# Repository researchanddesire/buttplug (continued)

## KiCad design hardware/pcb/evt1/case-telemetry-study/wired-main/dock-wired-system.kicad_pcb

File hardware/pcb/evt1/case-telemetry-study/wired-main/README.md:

# EVT wired dock Main

The cradle uses its four existing contacts for PC programming and standalone telemetry, with no cradle radio or antenna. The ESP32-C3 remains the USB device in both modes. A full-speed host on a separate RP2040 handles local USB while the STM32L071 retains the screen, buttons, watchdog and UV controls. Both upstream choices use the existing `CONTACT_5V` and ground. The RP2040 has no VBUS source tied to either connector.

The first build should use deliberate local mode selection. A host PC can advertise 1.5 A or 3 A, so `SOURCE_OK` only qualifies available power. It does not authorize taking the USB pair from a computer. A separate hardware PC lock clamps the local-enable logic low even with the two processors stalled. The host rail currently starts whenever qualified power and the lock/reset permissives are present. That lets the STM32 request local mode over the isolated two-wire interface. An independent local power request could reduce PC-mode draw in a later revision. The prototype recovery fixture must make the two shorting pads accessible with the product on the dock and the lid open, then power-cycle the dock with the short held. An enclosure-level access solution is still open.

## Data and recovery

U151 is the onsemi FSUSB42MUX, MSOP-10. Its common D+ and D− go to J102.3/.2. The first channel goes to J101 through retained U121. The second goes to RP2040 pins 47/46 through individual 27 Ω resistors at the RP2040. The common contact side gets separate low-capacitance shunt protection near J102. Its clamp returns to ground. U121 remains on the PC side with its existing `HOST_5V` reference. The switch has an independent active-low enable, a published 2 ns minimum break-before-make under the datasheet fixture conditions, and ±2 µA per-port power-off leakage over the stated test range. The 2 ns prevents overlap under those conditions. Firmware uses a much longer open interval for a planned USB detach.

At reset, the RP2040 request and blank outputs are low. With valid Main power, the switch defaults to PC. On startup use the existing delayed `CC_ENABLE` as the Main rail qualifier. A hardware falling `SOURCE_OK`, `SAFE_RESETn`, rail-valid or PC-lock condition removes local selection regardless of firmware. A forced or brownout transition can end a transfer. Hold the hardware PC lock during a service power-cycle before plug ROM entry if the dock is unresponsive.

In normal service, keep PC selected until the user requests local mode, the new branch is healthy, and the RP2040 USB host is initialized. Assert `USB_BREAK` for an initial 100 ms fixture interval, switch select while open, then remove the break. Return to PC by the same sequence after stopping local I/O. Clear the locally cached current reading on detach or timeout. If qualified source power is unavailable, return an unavailable state and keep PC ownership. Local and PC data access are exclusive. A PC-driven read can supply its own measurements during programming or diagnostics.

The existing Espressif console implements CDC over the native USB Serial/JTAG composite function. Espressif documents VID/PID `303a:1001` for its development-board example. TinyUSB's RP2040 host controller and CDC-ACM class are available. Identify the actual plug descriptors and endpoint/interface numbers before binding code. Enable the ACM host path, whitelist the intended device using the enumerated descriptor, and leave the vendor JTAG interface for the PC. Leave TinyUSB `CFG_TUH_CDC_LINE_CONTROL_ON_ENUM` undefined and avoid automatic DTR/RTS changes during local mounting because the ESP32-C3 USB Serial/JTAG interprets control line transitions for reset. Confirm hardware Power/Mode ROM entry and direct PC flashing with both case MCU reset points held and the recovery lock applied.

[RP2040 datasheet](https://datasheets.raspberrypi.com/rp2040/rp2040-datasheet.pdf) · [Raspberry Pi hardware design](https://pip-assets.raspberrypi.com/categories/814-rp2040/documents/RP-008279-DS-2-hardware-design-with-rp2040.pdf) · [onsemi FSUSB42](https://www.onsemi.com/pdf/datasheet/fsusb42-d.pdf) · [TinyUSB CDC host source](https://github.com/hathach/tinyusb/blob/master/src/class/cdc/cdc_host.c) · [Espressif USB console](https://docs.espressif.com/projects/esp-idf/en/stable/esp32c3/api-guides/usb-serial-jtag-console.html) · [Espressif descriptor example](https://docs.espressif.com/projects/rust/no_std-training/02_1_hardware.html) · [Espressif reset behavior](https://docs.espressif.com/projects/esptool/en/latest/esp32c3/esptool/advanced-options.html)

## Power

The existing hardware-qualified Type-C gate controls the separate `USB_HOST_5V` branch from the existing `HOST_5V` input. TPS2553QDBVRQ1 ILIM is tied directly to IN, the datasheet's 50/75/100 mA DC setting. The host target is at most 40 mA measured at J101 as a branch increment, giving 10 mA against the published minimum limit. This is a test limit. Raspberry Pi's BOOTSEL device-mode measurements give 21 mA at the sum of listed maximum average chip-rail values. The vendor's other workload exceeds 50 mA summed and neither workload represents local host traffic. Qualify actual clock speed, boot, QSPI flash, attach/reset, CDC traffic, SWD servicing, temperature and inrush. In particular, firmware does not write external flash during normal local service.

Reserve 104 mA for the new branch and all added control loads when qualified. At default USB100, the host branch is physically disabled and the existing 70 mA device and 10 mA UI allocations remain. A separate 1 mA allowance covers always-on additions in that mode. The 81 mA steady-state sum is separate from suspend, inrush, dynamic source downgrade, and recovery at a depleted plug battery. The existing device hardware limit can be as low as 34 mA in that mode. The existing PC bypass cannot guarantee standards compliance across USB suspend merely by meeting 100 mA while active.

To retain local USB during UV on a 1.5 A source, the proposed matching population is Main R107 40.2 kΩ 0.1% and UV R401/R501 both 4.22 Ω 1%. The new study computes both the fault ceiling and regulated UV operating point using the same physical path boundaries as the frozen source budget. The source limit and UV LED current must be considered as one assembly choice. The reduced drive requires fresh optical, leakage and thermal validation. Firmware must use the same 4.22 Ω conversion. Never fit a 104 mA branch alongside the frozen 34.8 kΩ and 3.65 Ω configuration for 1.5 A operation.

A separate TPS7A2033PDBVR LDO supplies the RP2040 and flash. Its 3.3 V output tolerance is ±1.5% in regulation. Verify at least 3.60 V at LDO IN and 3.135 V at RP2040 USB_VDD over load, transients and temperature. A local supervisor with a separate rail-valid output holds RUN low through bring-up. Decouple each IOVDD pin, both DVDD pins, USB_VDD and ADC_AVDD. Retain the Raspberry Pi 1 µF regulator input and output capacitors; use at least 1 µF effective local LDO input/output capacitance as the assembly acceptance. Reserve 10 µF nominal at the 3.3 V host regulator output and keep the bulk and startup profile in the inrush test. A contact-side rail monitor qualifies host attachment from J102.4. Its calculated falling threshold is 4.058–4.282 V, and the estimated rising upper corner is 4.408 V. Continuity and voltage at the actual plug contacts remain independent bench checks.

[TPS2553-Q1 datasheet](https://www.ti.com/lit/ds/symlink/tps2553-q1.pdf) · [TPS7A20 datasheet](https://www.ti.com/lit/ds/symlink/tps7a20.pdf) · [Frozen power budget](../../dock-safety/power-budget.json)

## Placement and bring-up

The mechanical read-only probe found a candidate B.Cu 20 × 20 × 1.5 mm volume centered at dock X−21/Y43. Its nominal floor clearance is 0.9 mm. Keep RP2040, ABM8-272-T3 crystal, 15 pF loads and 1 kΩ damping resistor on the same face and immediately adjacent to XIN/XOUT. The exact 6.3 × 3.6 mm mux courtyard passes at F.Cu X2/Y17 with 1.35 mm to the nearest rigid component. The central X0/Y17 site fails the 0.30 mm U114 courtyard margin. The X2 site still crosses the limiter return via. Both host and mux need routing and checks against the final populated native model, including ground reference continuity and the existing VBUS/cutoff routing. See the [package models and provenance](PACKAGE-MODELS.md).

Expose RP2040 SWDIO, SWCLK, RUN, GND and local VTREF as service pads for a target-powered probe. Fit the 10 kΩ external flash CS pull-up and expose BOOTSEL on the flash CS through 1 kΩ; the primary assembly programming plan is SWD while the local branch is qualified. A local BOOTSEL pad is not a second exposed USB programming connector. Keep the existing STM32 SWD and plug physical Power/Mode paths.

## Native KiCad source

Open [the transport schematic](dock-wired-transport.kicad_sch) with its
[project](dock-wired-transport.kicad_pro) to trace the connections across
Main, the display lid and the two UV boards. The transport and Main views
share six sheet files. [Native checks](native-checks.json) record zero KiCad
10.0.8 ERC findings in both views and verify that every Main terminal agrees
with the transport netlist. The combined `native.xml` retains all 303
components and 1,077 terminals for firmware, harness and UV checks. The
[wired firmware targets](../../../../../dock-firmware/wired-main/README.md)
add I²C mode selection and fresh temperature on the display. Winbond stencil
review, PCB routing, installed access and powered USB/UV tests remain open.

Open [the working EVT Main project](dock-wired-system.kicad_pro) for the
[six-sheet schematic](dock-wired-system.kicad_sch) and
[active PCB](dock-wired-system.kicad_pcb). Finish routing and fit on this
board. It incorporates the fixed-position
oscillator and crossing routes, contact-voltage valid, limiter-fault
readback, ground stitching and the latest 3.3 V supply branches. The host
I²C clock, the qualified USB enable branch from U153.3 to U157 and the
always-on reset control from U157.13 to U163.6 are routed.
R163.1 joins the USB enable net. Host I²C data joins U201.6, U162.2 and
pull-up R165.1. TP156 joins the USB host 3.3 V rail for probing. C155.1
joins the Main 3.3 V rail. The adjacent MCU_STOPn and USB_HOST_3V3 traces
retain their widths and layers through local detours. U155.2 connects to
ground and C153.2 has a dedicated return stitch. The LID_FB detour retains
both C172.2 thermal spokes. R156.1 reaches C159.1 on 3V3 through 1.346 mm
of 0.20 mm copper. The adjacent MCU_ARM detour retains its 0.20 mm width.
C161.2 connects to an existing ground via on B.Cu, closing the last ground
open. C161.1 joins 3V3 through the rerouted R165.2 branch.
The RP2040 RUN pad U160.26 joins U155.6. The adjacent monitor clock now uses
a 0.324 mm bridge on F.Cu to its existing plane transition. The translator
RUN leg remains open. The [native routing audit](active-routing.json)
records 13 opens and zero other
PCB design-rule findings. The new 1.1 V branch connects C177.1 to U160.23. The monitor
I²C clock detours on B.Cu. R155.1 and the U155 reset supervisor supply
join 3.3 V. R165.2 reaches the 3.3 V pull-up supply with U162's ground
preserved by a new return trace to the existing stitch. R157.2 joins the
local run net at U163.1. The PC recovery test pad TP151, U157.4 and pull-up
R156.2 now share `PC_LOCKn`. The adjacent Type-C sense trace detours around
this connection. Check installed access and cold-start recovery on the bench.
U160.19 now connects to the existing B.Cu ground fill through a 1.15 mm trace.
The inner ground plane remains continuous with the same fill within 1 mm
of the oscillator traces. U160.50 still needs a local 100 nF core bypass.
C178.1 is 6.14 mm away in a straight line, and the clearance-clean route
would add 14.28 mm of copper plus layer transitions. Keep the oscillator
positions and review the core bypass placement before closing this branch.
Finish the remaining core rail, run, host enable, I²C and other unconnected
nets before generating supplier artwork.
[RP2040 hardware design guide](https://datasheets.raspberrypi.com/rp2040/hardware-design-with-rp2040.pdf)

The [editable Hall receiver integration](../../dock-safety/wired-hall-head/main-integration/README.md)
replays on the Main and transport schematics. It adds the two receiver
channels and their independent thermostat inputs, plus the contact branch
limiter. Native ERC passes in both views. The overlay grounds both emitter
enable inputs during integration. Incorporate it into the Main PCB layout
and verify the actual cutoff paths and measurements before powering the UV
modules.

The native audit verifies 799 unique Main pad-to-net assignments and zero
schematic parity findings. The mounting holes are board-only mechanical
features. The 14 bare-copper test points remain connected and are excluded
from the parts BOM. Use the Main project for PCB updates and the transport
project for cross-board tracing.

The [Main parts selection](main-order-selection.json) covers 200 fitted parts
across 70 manufacturer part lines. See the
[passive part evidence](passive-parts-selection.json) and the
[matched UV base and lid supplier quotes](uv-assembly/README.md). The quote
packages bind Main R107 at 40.2 kΩ, R401/R501 at 4.22 Ω and the wired
firmware profile as one configuration.

The [native package fit study](../../../../cad/evt1-assembly/dock-harness-trial/wired-main-space-review/README.md#native-package-fit)
checks the 62 selected package models against the saved dock. The lowest
nominal shell clearance is 0.765 mm. The moved U158 clears the shell and
other package models in its own check. The [docked recovery study](../../../../cad/evt1-assembly/dock-harness-trial/wired-main-space-review/recovery-access/README.md)
details the default-source cable and optional hardware-lock access.

Replay from this directory with `python3 contract.py`, `python3 build_source.py --stock-footprints <KiCad 10 footprint library directory>` and `python3 check_native.py --kicad-cli <KiCad 10.0.8 executable>`.

## Product lid cutoff

The [Hall head project](../../dock-safety/wired-hall-head/wired-hall-head.kicad_pro)
uses the same chamfered 8.8 × 16 mm PCB at both stations. The substrate and
component-height envelopes clear the closed shells, liners and reference
mounts. The head is routed and the [two-board quote](../../dock-safety/wired-hall-head/assembly-quote/README.md)
is ready. Finish mount retention and tail strain relief before fitting it to
the dock.

Integrate two supervised Hall closure channels in the wired-specific
`dock-safety` sheet. Retain the thermostats on J621/J622 pins 7–8, the
430 Ω returns and U613 sensing. Feed the thermostats from separately
protected, low-drop branches of qualified `LOOP_5V` to preserve contact
current. Combine each thermal result with its corresponding Hall permit
in a separate fail-low hardware gate. Keep `LOOP_A` and `LOOP_B` as the
outputs to the existing UV cutoff logic. The fitted gate, its fault behavior
and the sensor/target mounts still need integration. Verify cutoff during
opening and check finished units for UV-C leakage around the seam, hinge
and ports.

The two Hall supplies and thermal branch limits must fit within the 1.5 A
source budget during faults. At the existing 40.2 kΩ R107 value, 15.51 mA
remains ahead of Hall integration. Evaluating 41.2 kΩ with the existing
4.22 Ω UV resistors raises that allowance to 31.85 mA. The same calculated
UV load is 563.63 mA, with an 11.33 mA margin to the low end of the new
limiter range. A bounded feed design uses three 182 Ω resistors in series
per Hall head and budgets up to 3.0 mA steady-state per head. The 41.2 kΩ
case leaves 2.93 mA of modeled source margin with both head feeds shorted.
Verify source and driver startup, connector faults and head placement before
changing the active circuit or R107 value.
[TI TPS2553 limit equations](https://www.ti.com/lit/ds/symlink/tps2553-q1.pdf)

The staged receiver used 2.3 mA as the low end of the intact signature.
TI specifies 2.3 mA typical and 2.8 mA maximum for the DRV5021, without a
guaranteed minimum. The receiver needs a bounded intact signature across
supply and temperature. The staged receiver stays held low until its
electrical and installed cutoff checks pass.
[TI DRV5021 electrical characteristics](https://www.ti.com/lit/ds/symlink/drv5021.pdf#page=4)

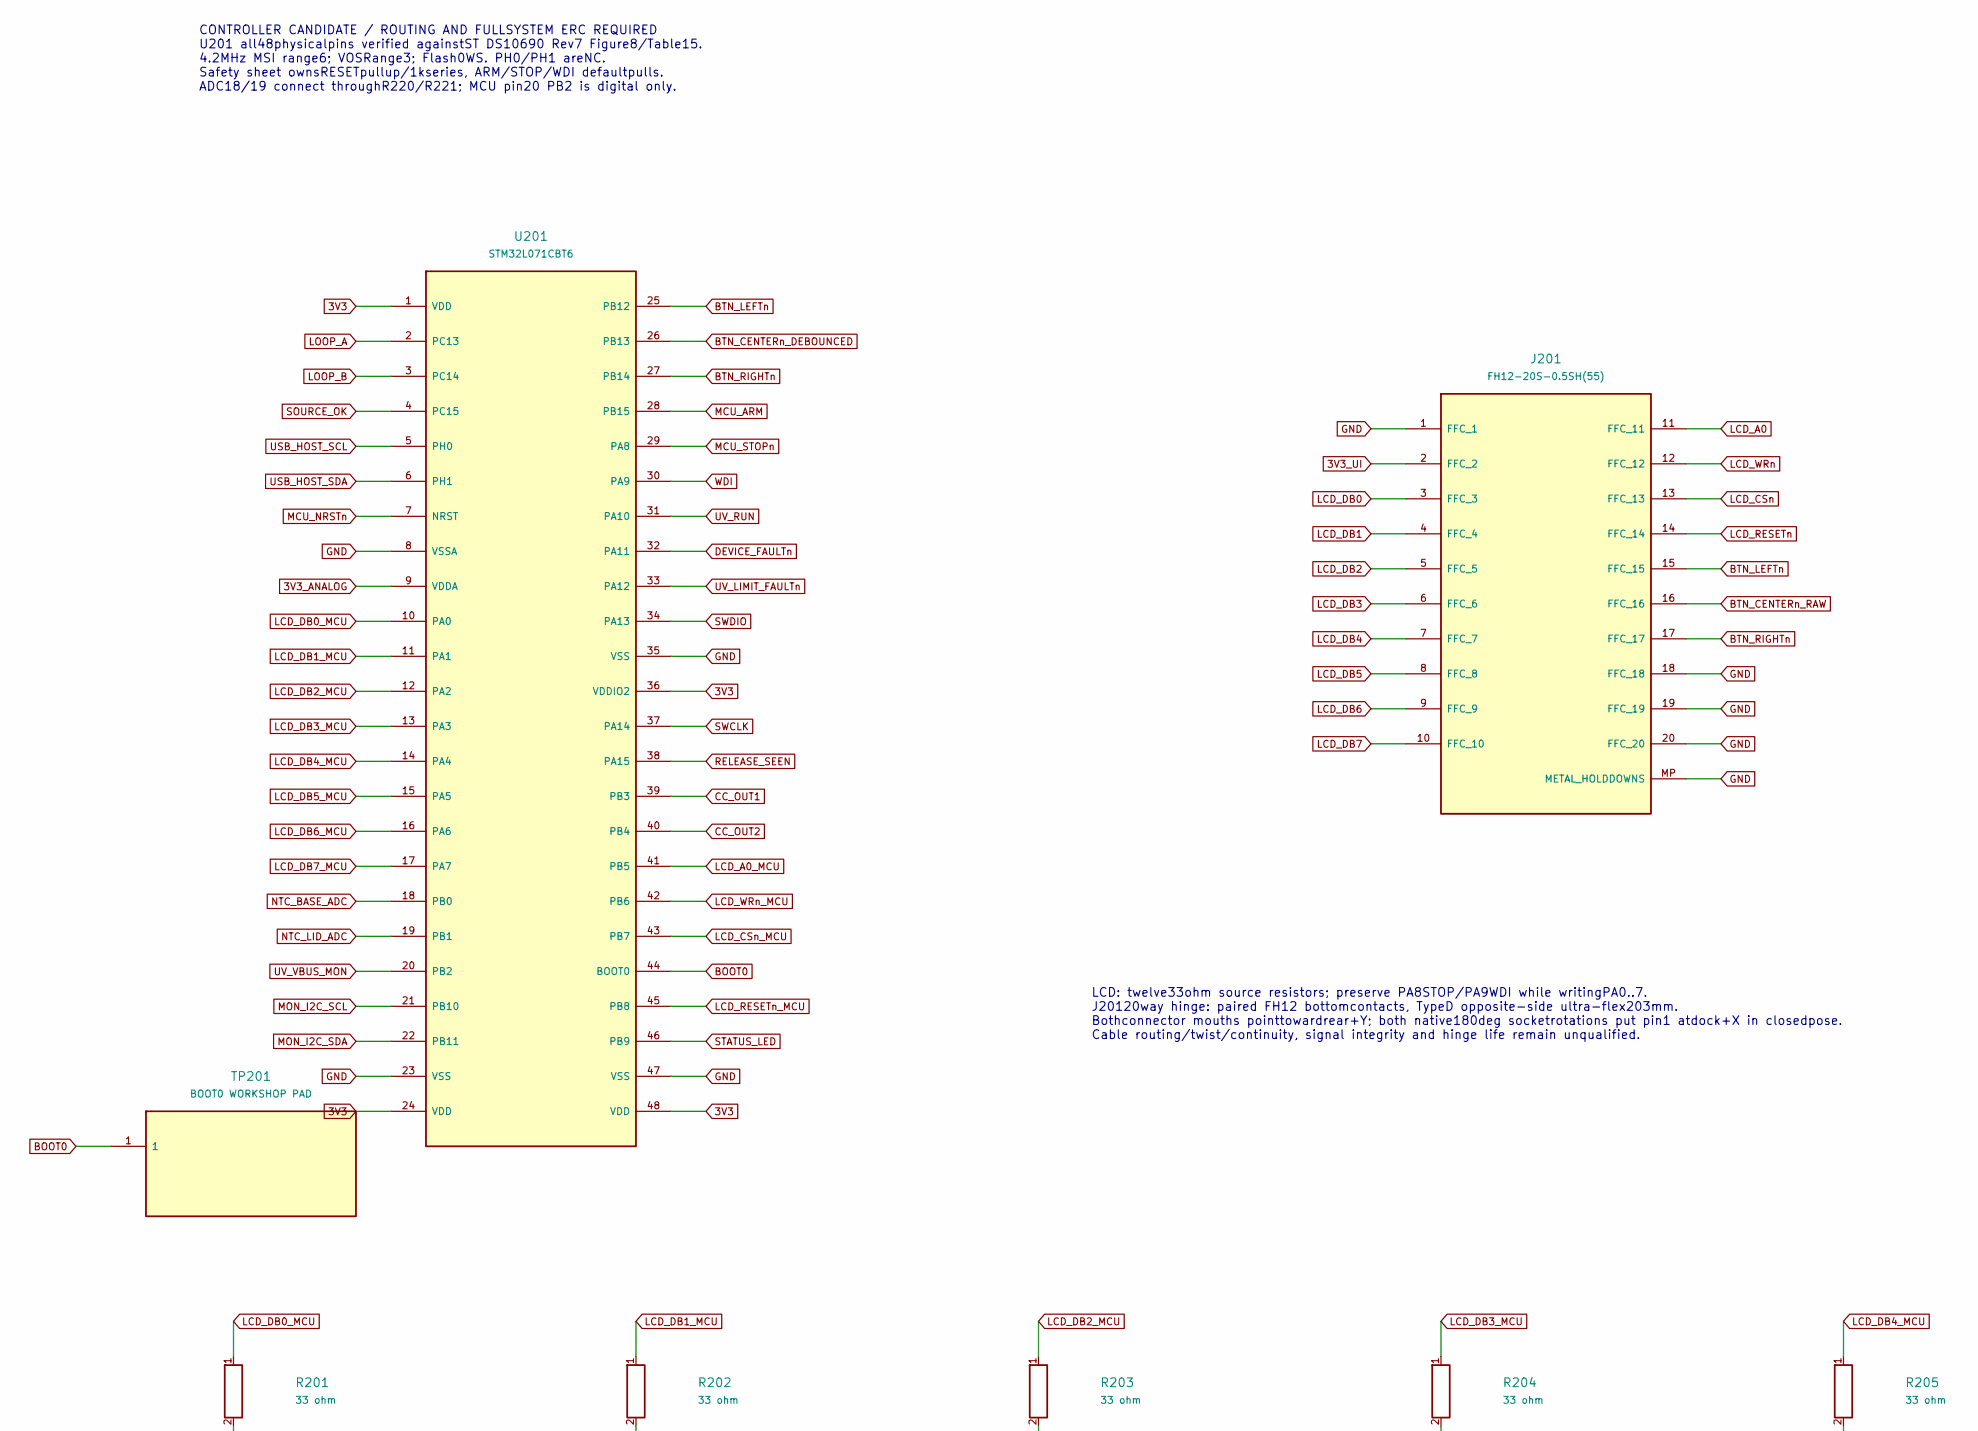
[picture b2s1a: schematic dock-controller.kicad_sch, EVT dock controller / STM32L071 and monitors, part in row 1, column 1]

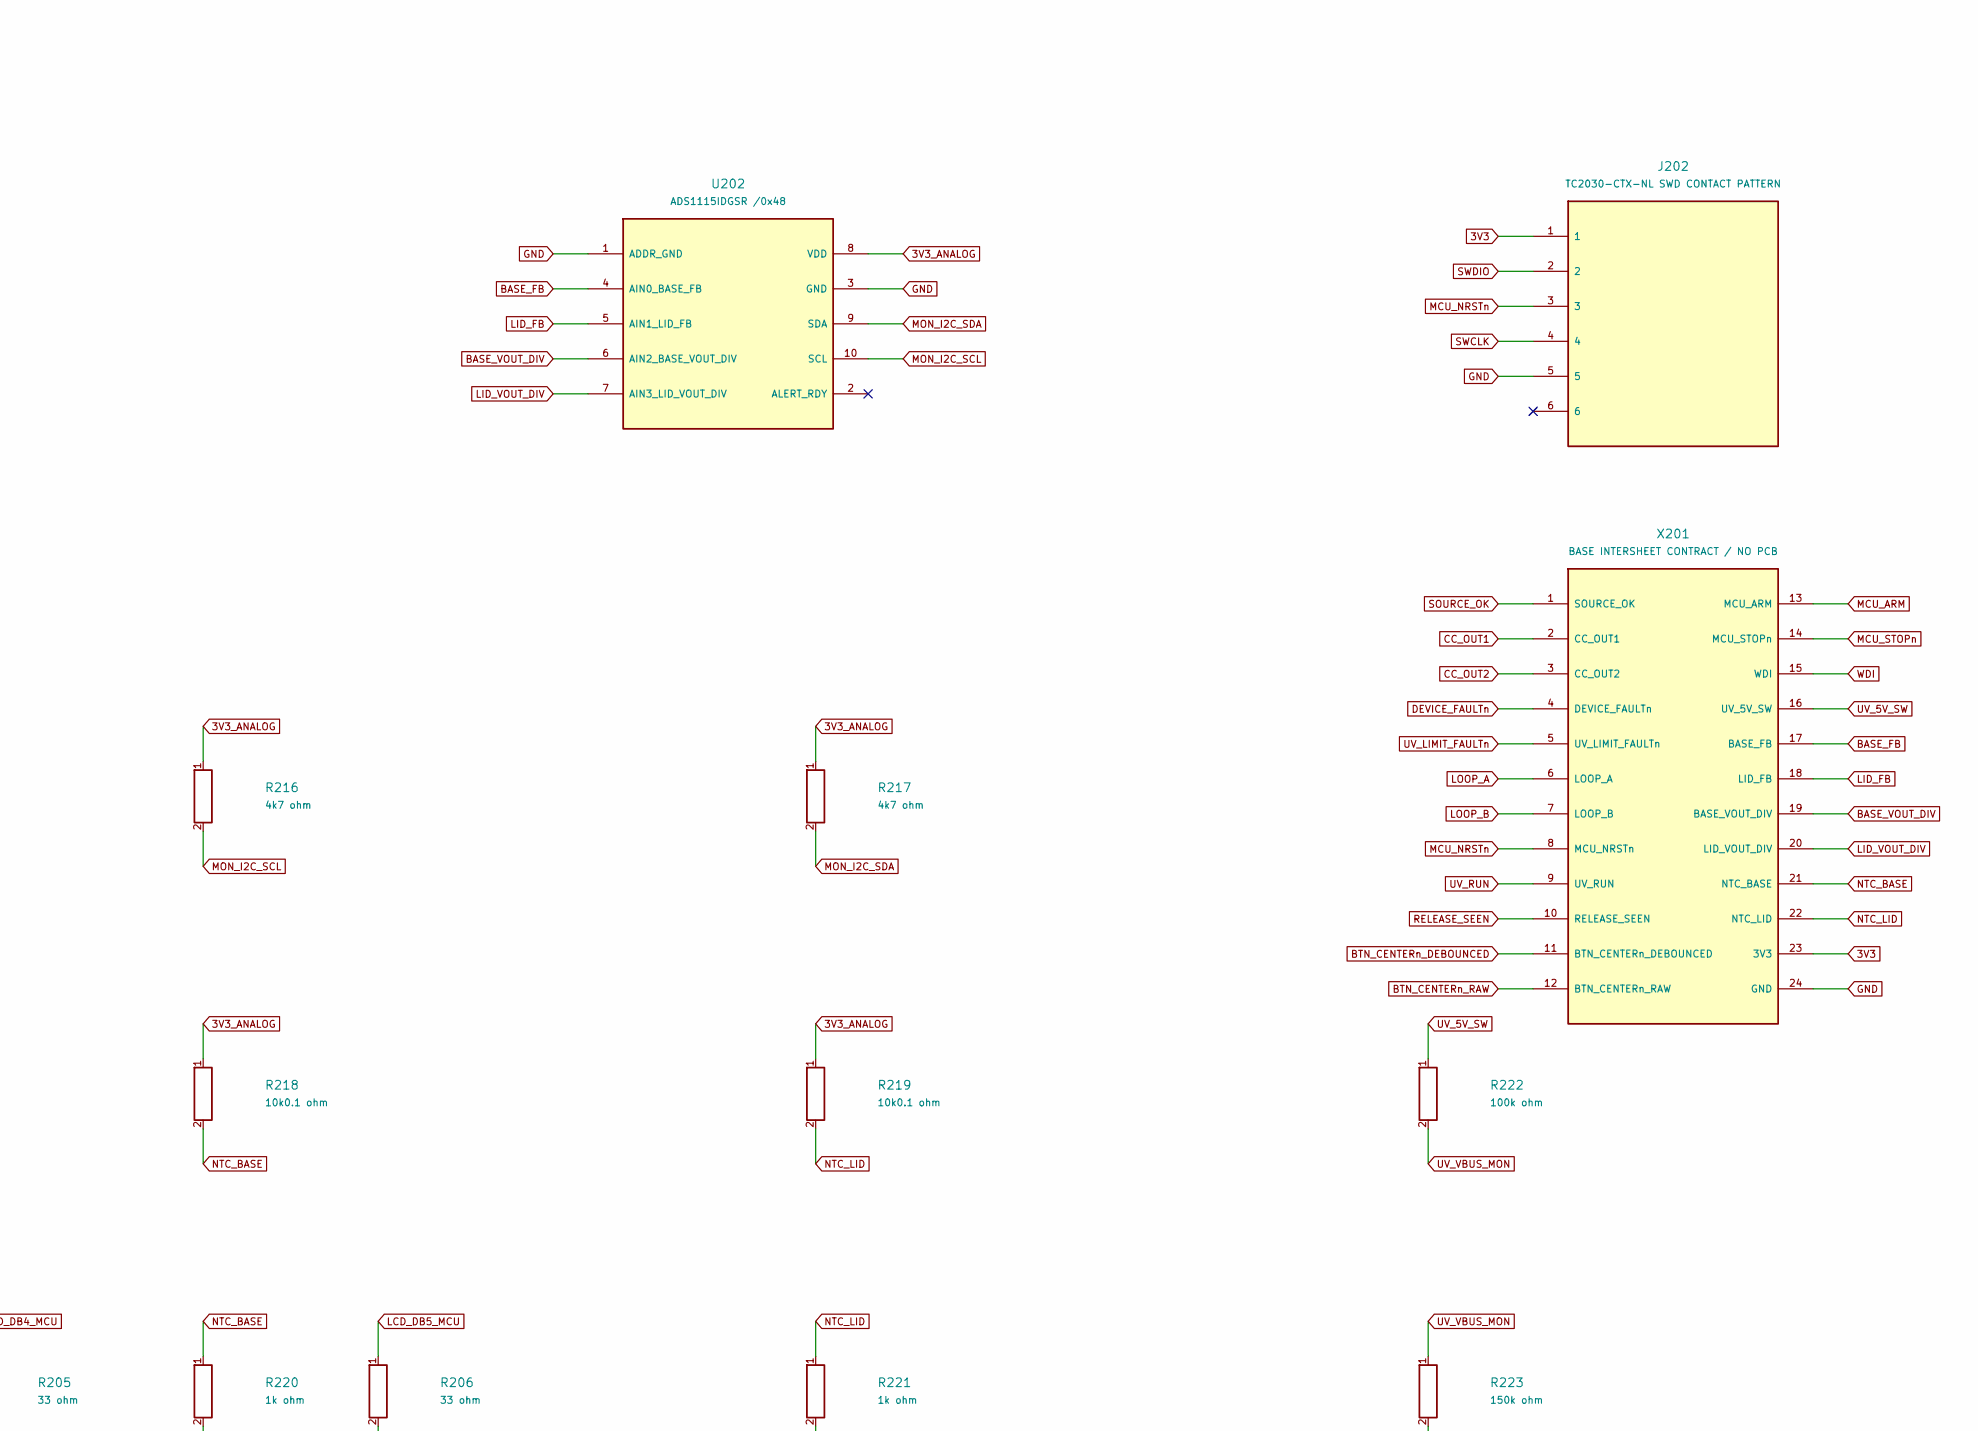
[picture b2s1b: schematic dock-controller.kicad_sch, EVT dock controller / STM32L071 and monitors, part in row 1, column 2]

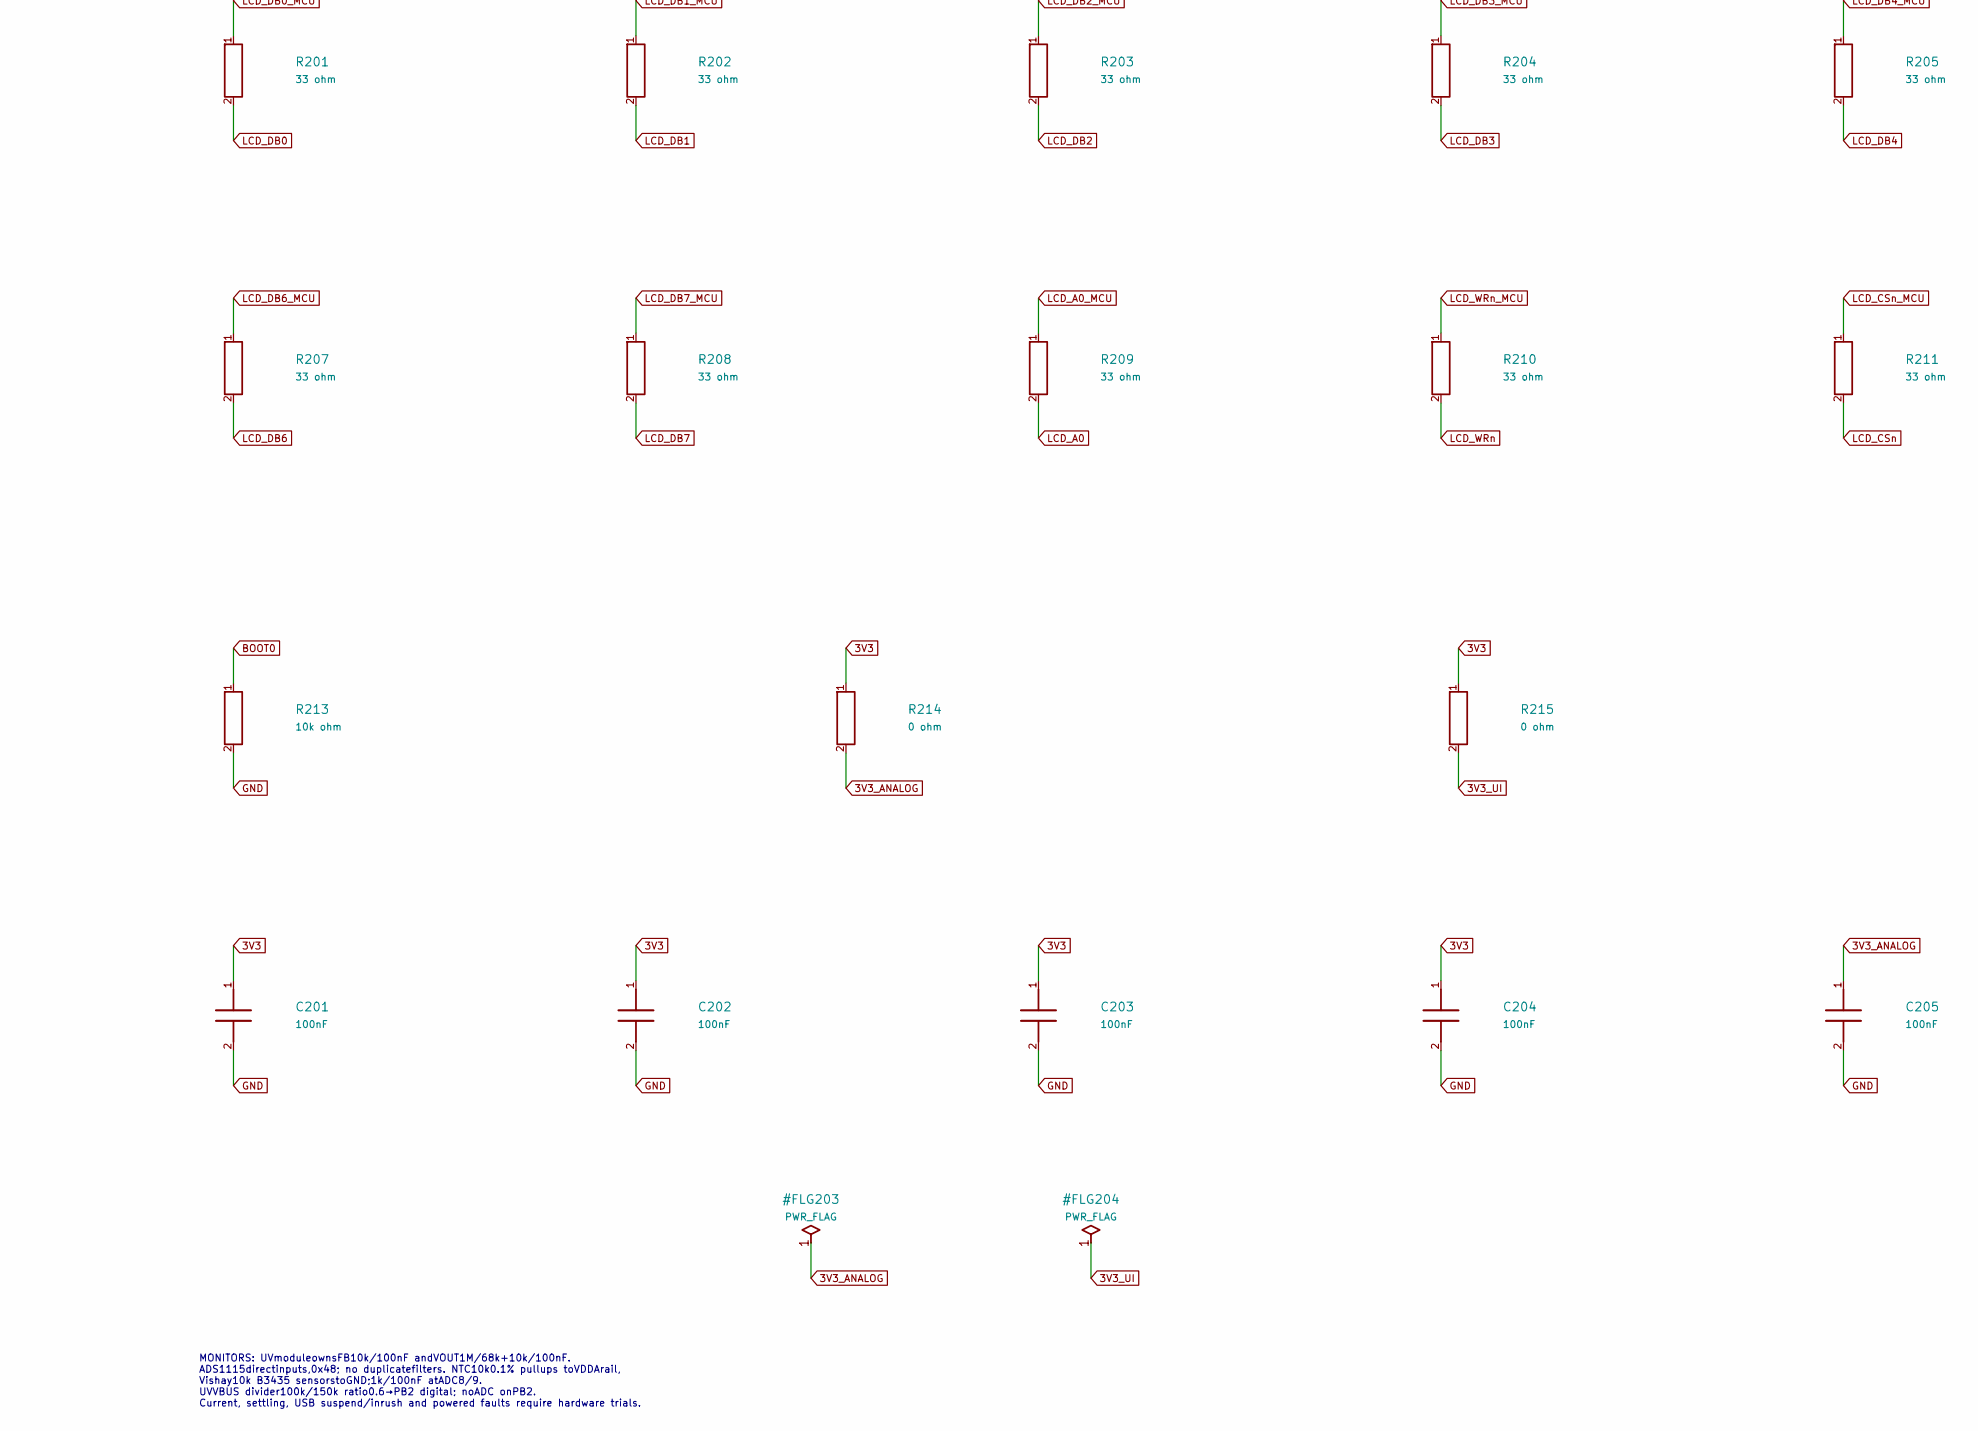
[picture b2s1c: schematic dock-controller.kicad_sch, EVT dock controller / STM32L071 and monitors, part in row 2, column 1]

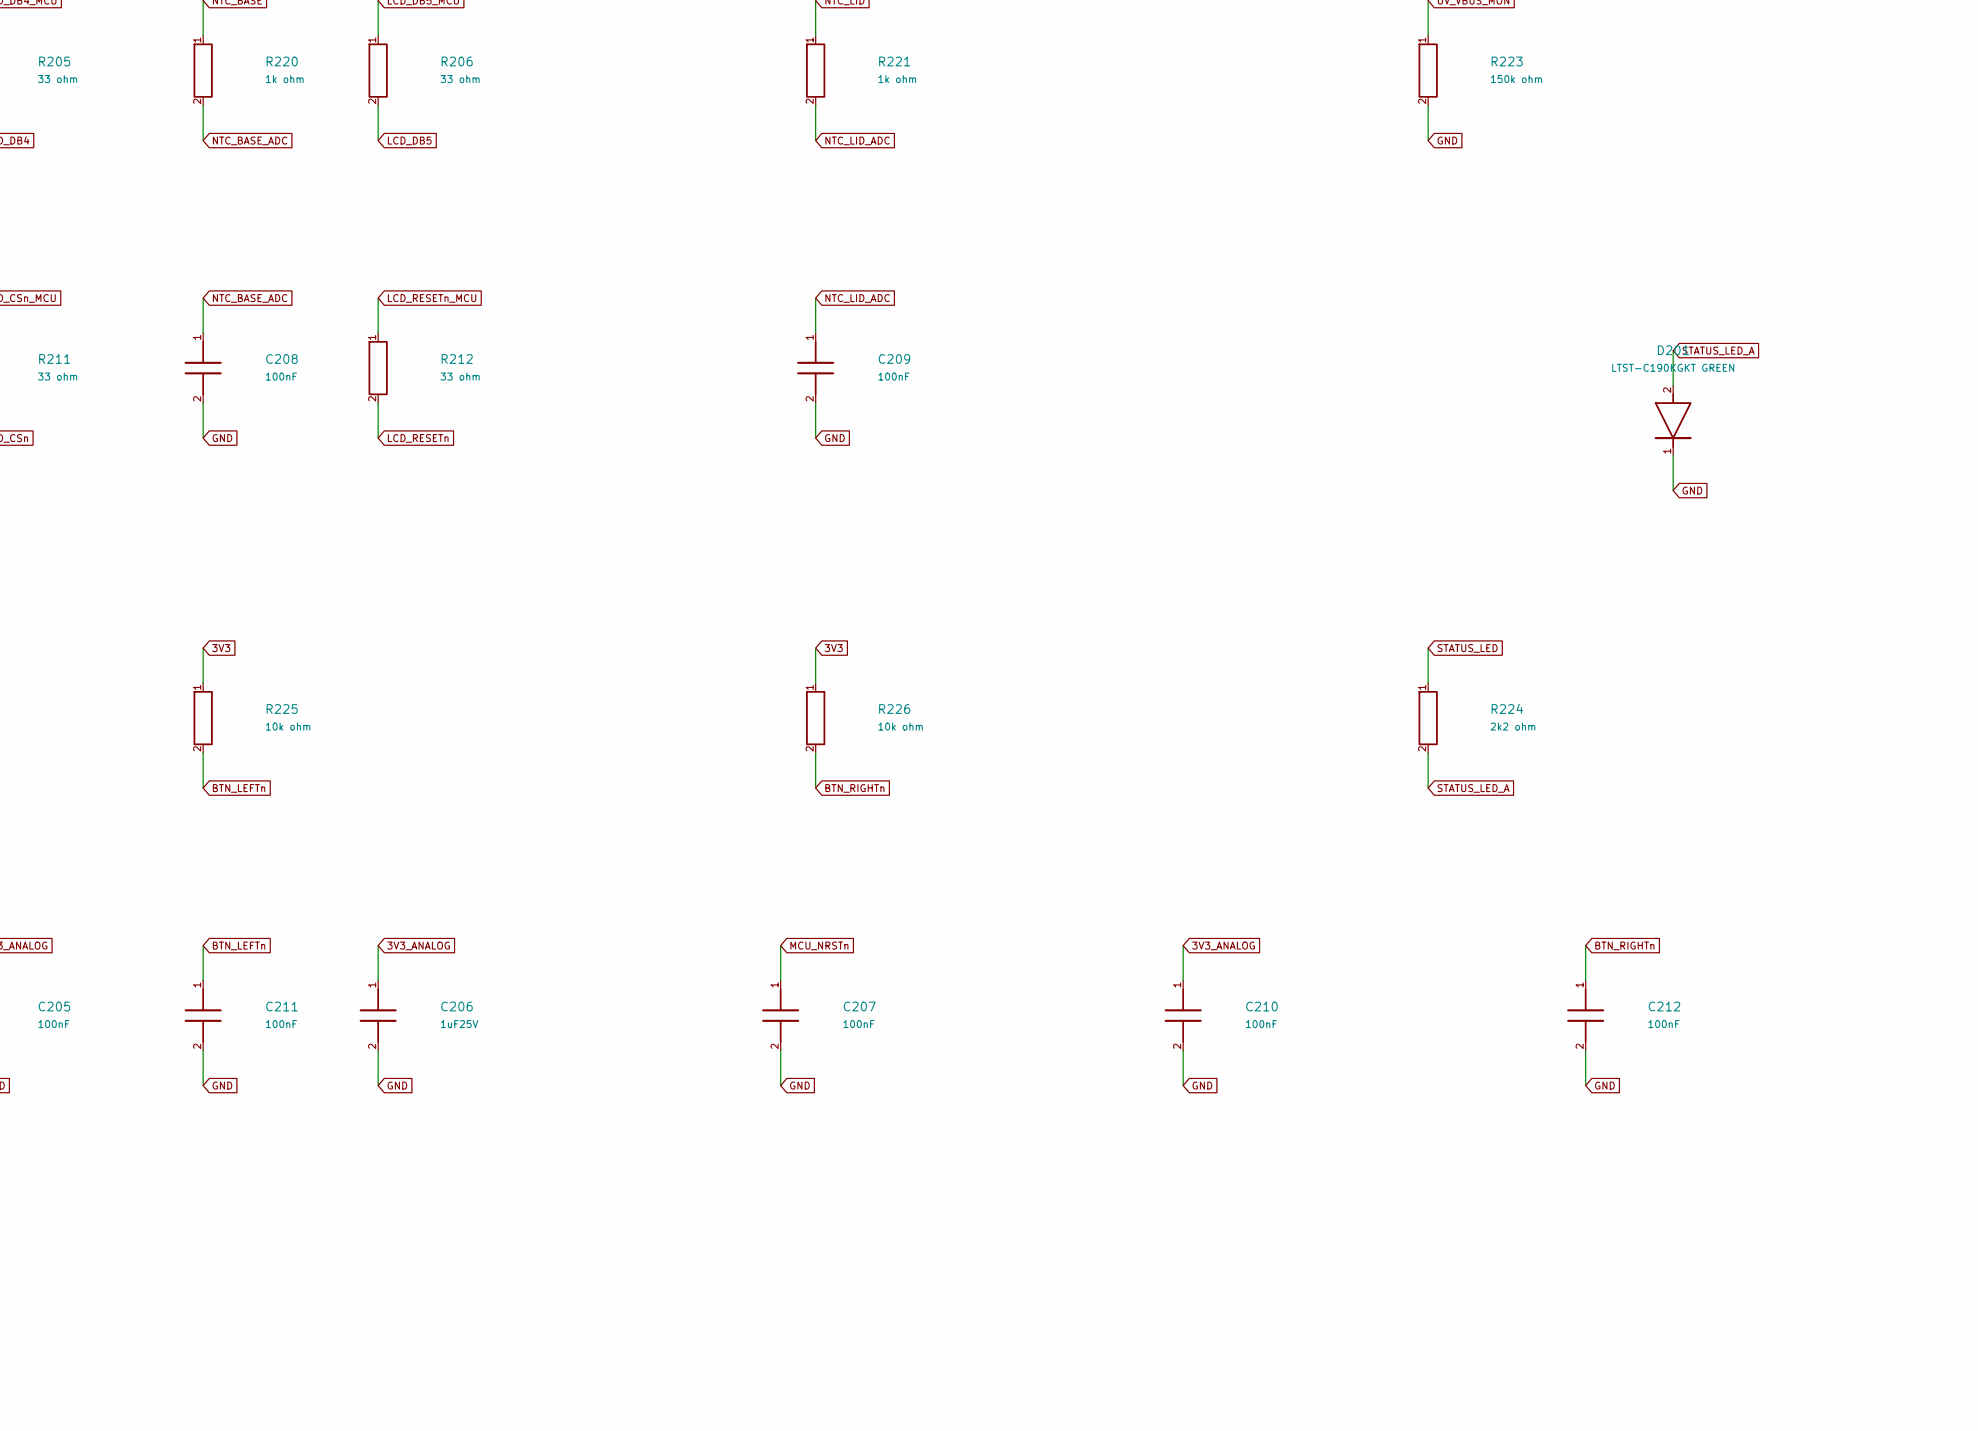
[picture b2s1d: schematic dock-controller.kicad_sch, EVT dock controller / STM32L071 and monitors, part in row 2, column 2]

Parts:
C201, C202, C203, C204, C205, C207, C208, C209, C210, C211, C212: 100nF; C_0402_1005Metric; MPN GRM155R71C104KA88D
C206: 1uF25V; C_0603_1608Metric; MPN C1608X7R1E105K080AB
D201: LTST-C190KGKT GREEN; LED_0603_1608Metric; MPN LTST-C190KGKT
J201: FH12-20S-0.5SH(55); Hirose_FH12-20S-0.5SH_1x20-1MP_P0.50mm_Horizontal; MPN FH12-20S-0.5SH(55)
J202: TC2030-CTX-NL SWD CONTACT PATTERN; Tag-Connect_TC2030-IDC-NL_2x03_P1.27mm_Vertical; MPN –
R201, R202, R203, R204, R205, R206, R207, R208, R209, R210, R211, R212: 33 ohm; R_0603_1608Metric; MPN RC0603FR-0733RL
R213, R225, R226: 10k ohm; R_0603_1608Metric; MPN RC0603FR-0710KL
R214, R215: 0 ohm; R_0603_1608Metric; MPN RC0603JR-070RL
R216, R217: 4k7 ohm; R_0603_1608Metric; MPN RC0603FR-074K7L
R218, R219: 10k0.1 ohm; R_0603_1608Metric; MPN RT0603BRD0710KL
R220, R221: 1k ohm; R_0603_1608Metric; MPN RC0603FR-071KL
R222: 100k ohm; R_0603_1608Metric; MPN RC0603FR-07100KL
R223: 150k ohm; R_0603_1608Metric; MPN RC0603FR-07150KL
R224: 2k2 ohm; R_0603_1608Metric; MPN RC0603FR-072K2L
TP201: BOOT0 WORKSHOP PAD; TestPoint_Pad_D1.0mm; MPN –
U201: STM32L071CBT6; LQFP-48_7x7mm_P0.5mm; MPN STM32L071CBT6
U202: ADS1115IDGSR /0x48; VSSOP-10_3x3mm_P0.5mm; MPN ADS1115IDGSR
X201: BASE INTERSHEET CONTRACT / NO PCB; MPN –

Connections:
3V3: C201.1, C202.1, C203.1, C204.1, J202.1, R214.1, R215.1, R225.1, R226.1, U201.1 (VDD), U201.24 (VDD), U201.36 (VDDIO2), U201.48 (VDD), X201.23 (3V3); also elsewhere on the board
3V3_ANALOG: C205.1, C206.1, C210.1, R214.2, R216.1, R217.1, R218.1, R219.1, U201.9 (VDDA), U202.8 (VDD)
3V3_UI: J201.2 (FFC_2), R215.2
BASE_FB: U202.4 (AIN0_BASE_FB), X201.17 (BASE_FB); also elsewhere on the board
BASE_VOUT_DIV: U202.6 (AIN2_BASE_VOUT_DIV), X201.19 (BASE_VOUT_DIV); also elsewhere on the board
BOOT0: R213.1, TP201.1, U201.44 (BOOT0)
BTN_CENTERn_DEBOUNCED: U201.26 (PB13), X201.11 (BTN_CENTERn_DEBOUNCED); also elsewhere on the board
BTN_CENTERn_RAW: J201.16 (FFC_16), X201.12 (BTN_CENTERn_RAW); also elsewhere on the board
BTN_LEFTn: C211.1, J201.15 (FFC_15), R225.2, U201.25 (PB12)
BTN_RIGHTn: C212.1, J201.17 (FFC_17), R226.2, U201.27 (PB14)
CC_OUT1: U201.39 (PB3), X201.2 (CC_OUT1); also elsewhere on the board
CC_OUT2: U201.40 (PB4), X201.3 (CC_OUT2); also elsewhere on the board
DEVICE_FAULTn: U201.32 (PA11), X201.4 (DEVICE_FAULTn); also elsewhere on the board
GND: C201.2, C202.2, C203.2, C204.2, C205.2, C206.2, C207.2, C208.2, C209.2, C210.2, C211.2, C212.2, D201.1 (2), J201.1 (FFC_1), J201.18 (FFC_18), J201.19 (FFC_19), J201.20 (FFC_20), J201.MP (METAL_HOLDDOWNS), J202.5, R213.2, R223.2, U201.8 (VSSA), U201.23 (VSS), U201.35 (VSS), U201.47 (VSS), U202.1 (ADDR_GND), U202.3 (GND), X201.24 (GND); also elsewhere on the board
LCD_A0: J201.11 (FFC_11), R209.2
LCD_A0_MCU: R209.1, U201.41 (PB5)
LCD_CSn: J201.13 (FFC_13), R211.2
LCD_CSn_MCU: R211.1, U201.43 (PB7)
LCD_DB0: J201.3 (FFC_3), R201.2
LCD_DB0_MCU: R201.1, U201.10 (PA0)
LCD_DB1: J201.4 (FFC_4), R202.2
LCD_DB1_MCU: R202.1, U201.11 (PA1)
LCD_DB2: J201.5 (FFC_5), R203.2
LCD_DB2_MCU: R203.1, U201.12 (PA2)
LCD_DB3: J201.6 (FFC_6), R204.2
LCD_DB3_MCU: R204.1, U201.13 (PA3)
LCD_DB4: J201.7 (FFC_7), R205.2
LCD_DB4_MCU: R205.1, U201.14 (PA4)
LCD_DB5: J201.8 (FFC_8), R206.2
LCD_DB5_MCU: R206.1, U201.15 (PA5)
LCD_DB6: J201.9 (FFC_9), R207.2
LCD_DB6_MCU: R207.1, U201.16 (PA6)
LCD_DB7: J201.10 (FFC_10), R208.2
LCD_DB7_MCU: R208.1, U201.17 (PA7)
LCD_RESETn: J201.14 (FFC_14), R212.2
LCD_RESETn_MCU: R212.1, U201.45 (PB8)
LCD_WRn: J201.12 (FFC_12), R210.2
LCD_WRn_MCU: R210.1, U201.42 (PB6)
LID_FB: U202.5 (AIN1_LID_FB), X201.18 (LID_FB); also elsewhere on the board
LID_VOUT_DIV: U202.7 (AIN3_LID_VOUT_DIV), X201.20 (LID_VOUT_DIV); also elsewhere on the board
LOOP_A: U201.2 (PC13), X201.6 (LOOP_A); also elsewhere on the board
LOOP_B: U201.3 (PC14), X201.7 (LOOP_B); also elsewhere on the board
MCU_ARM: U201.28 (PB15), X201.13 (MCU_ARM); also elsewhere on the board
MCU_NRSTn: C207.1, J202.3, U201.7 (NRST), X201.8 (MCU_NRSTn); also elsewhere on the board
MCU_STOPn: U201.29 (PA8), X201.14 (MCU_STOPn); also elsewhere on the board
MON_I2C_SCL: R216.2, U201.21 (PB10), U202.10 (SCL)
MON_I2C_SDA: R217.2, U201.22 (PB11), U202.9 (SDA)
NTC_BASE: R218.2, R220.1, X201.21 (NTC_BASE); also elsewhere on the board
NTC_BASE_ADC: C208.1, R220.2, U201.18 (PB0)
NTC_LID: R219.2, R221.1, X201.22 (NTC_LID); also elsewhere on the board
NTC_LID_ADC: C209.1, R221.2, U201.19 (PB1)
RELEASE_SEEN: U201.38 (PA15), X201.10 (RELEASE_SEEN); also elsewhere on the board
SOURCE_OK: U201.4 (PC15), X201.1 (SOURCE_OK); also elsewhere on the board
STATUS_LED: R224.1, U201.46 (PB9)
STATUS_LED_A: D201.2 (1), R224.2
SWCLK: J202.4, U201.37 (PA14)
SWDIO: J202.2, U201.34 (PA13)
USB_HOST_SCL: U201.5 (PH0); also elsewhere on the board
USB_HOST_SDA: U201.6 (PH1); also elsewhere on the board
UV_5V_SW: R222.1, X201.16 (UV_5V_SW); also elsewhere on the board
UV_LIMIT_FAULTn: U201.33 (PA12), X201.5 (UV_LIMIT_FAULTn); also elsewhere on the board
UV_RUN: U201.31 (PA10), X201.9 (UV_RUN); also elsewhere on the board
UV_VBUS_MON: R222.2, R223.1, U201.20 (PB2)
WDI: U201.30 (PA9), X201.15 (WDI); also elsewhere on the board

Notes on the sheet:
CONTROLLER CANDIDATE / ROUTING AND FULLSYSTEM ERC REQUIRED U201 all48physicalpins verified againstST DS10690 Rev7 Figure8/Table15. 4.2MHz MSI range6; VOSRange3; Flash0WS. PH0/PH1 areNC. Safety sheet ownsRESETpullup/1kseries, ARM/STOP/WDI defaultpulls. ADC18/19 connect throughR220/R221; MCU pin20 PB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
LCD: twelve33ohm source resistors; preserve PA8STOP/PA9WDI while writingPA0..7. J20120way hinge: paired FH12 bottomcontacts, TypeD opposite-side ultra-flex203mm. Bothconnector mouths pointtowardrear+Y; both native180deg socketrotations put pin1 atdock+X in closedpose. Cable routing/twist/continuity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
MONITORS: UVmoduleownsFB10k/100nF andVOUT1M/68k+10k/100nF. ADS1115directinputs,0x48; no duplicatefilters. NTC10k0.1% pullups toVDDArail, Vishay10k B3435 sensorstoGND;1k/100nF atADC8/9. UVVBUS divider100k/150k ratio0.6→PB2 digital; noADC onPB2. Current, settling, USB suspend/inrush and powered fault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

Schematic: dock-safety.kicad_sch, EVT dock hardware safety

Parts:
C602, C606, C607, C608, C609, C610, C611, C612, C613, C614, C615, C616: 100nF16V; C_0402_1005Metric; MPN GRM155R71C104KA88D
C620, C621, C622: 1uF25V; C_0603_1608Metric; MPN C1608X7R1E105K080AB
C623, C624: 1nF50V C0G; C_0603_1608Metric; MPN C1608C0G1H102J080AA
J601, J602: SM02B-GHS-TB; JST_GH_SM02B-GHS-TB_1x02-1MP_P1.25mm_Horizontal; MPN SM02B-GHS-TB(LF)(SN)
J621, J622: SM08B-GHS-TB; JST_GH_SM08B-GHS-TB_1x08-1MP_P1.25mm_Horizontal; MPN SM08B-GHS-TB(LF)(SN)
R601, R603, R607, R616: 10k 1%; R_0603_1608Metric; MPN RC0603FR-0710KL
R602, R604, R605, R608, R612, R613, R617: 100k 1%; R_0603_1608Metric; MPN RC0603FR-07100KL
R606: 1k 1%; R_0603_1608Metric; MPN RC0603FR-071KL
R610, R611: 330R 1%; R_0805_2012Metric; MPN CRCW0805330RFKEA
R614, R615: 430R 1%; R_0805_2012Metric; MPN CRCW0805430RFKEA
R618: 1M 1%; R_0603_1608Metric; MPN RC0603FR-071ML
R619: 47k 1%; R_0603_1608Metric; MPN RC0603FR-0747KL
S601, S602: D2F-01L remote; MPN D2F-01L
TP601: MCU_NRSTn; TestPoint_Pad_D1.0mm; MPN Cu_D1.0mm_test_land
TP602: BASE_FB; TestPoint_Pad_D1.0mm; MPN Cu_D1.0mm_test_land
TP603: LID_FB; TestPoint_Pad_D1.0mm; MPN Cu_D1.0mm_test_land
TP604: BASE_VOUT_DIV; TestPoint_Pad_D1.0mm; MPN Cu_D1.0mm_test_land
TP605: LID_VOUT_DIV; TestPoint_Pad_D1.0mm; MPN Cu_D1.0mm_test_land
TP606: NTC_BASE; TestPoint_Pad_D1.0mm; MPN Cu_D1.0mm_test_land
TP607: NTC_LID; TestPoint_Pad_D1.0mm; MPN Cu_D1.0mm_test_land
U602: TPS22919DCKR; SOT-363_SC-70-6; MPN TPS22919DCKR
U606: TPS3431SDRBR; Texas_DRB0008A_3x3mm_P0.65_EP_Fingers; MPN TPS3431SDRBR
U607, U616: TPS3808G33DBVR; SOT-23-6; MPN TPS3808G33DBVR
U608: MAX6816EUS+T; SOT-143; MPN MAX6816EUS+T
U609: SN74LVC74APWR; TSSOP-14_4.4x5mm_P0.65mm; MPN SN74LVC74APWR
U610, U611: TPS22992RXPR; Texas_RXP0008A_1.25x1.5mm_Asymmetric; MPN TPS22992RXPR
U612: SN74HCS21PWR; TSSOP-14_4.4x5mm_P0.65mm; MPN SN74HCS21PWR
U613, U614: SN74LVC2G17DCKR; SOT-363_SC-70-6; MPN SN74LVC2G17DCKR
U615: SN74HCS08PWR; TSSOP-14_4.4x5mm_P0.65mm; MPN SN74HCS08PWR

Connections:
3V3: C606.1, C607.1, C608.1, C609.1, C612.1, C613.1, C614.1, C615.1, C616.1, R601.1, R603.1, R607.1, R608.1, R616.1, R617.1, U606.1 (VDD), U606.3 (EN_HARD_HIGH), U606.5 (SET1_HIGH), U607.3 (MR_N), U607.5 (SENSE), U607.6 (VDD), U608.4 (VCC), U609.2 (1D), U609.4 (1PRE_N), U609.10 (2PRE_N), U609.14 (VCC), U612.13 (2D), U612.14 (VCC), U613.5 (VCC), U614.5 (VCC), U615.14 (VCC), U616.5 (SENSE), U616.6 (VDD); also elsewhere on the board
ARM_D: U609.12 (2D_ARM), U615.3 (1Y_ARM_D)
BASE_FB: J621.4, TP602.1; also elsewhere on the board
BASE_THERM_SEND: J601.2, J621.7, S601.NO (NO_LID_CLOSED)
BASE_VOUT_DIV: J621.5, TP604.1; also elsewhere on the board
BTN_CENTER_PRESSED: R619.1, U614.3 (2A_LOOP_B); also elsewhere on the board
BTN_CENTERn_DEBOUNCED: U608.3 (OUT_DEBOUNCED), U614.1 (1A_LOOP_A); also elsewhere on the board
BTN_CENTERn_RAW: R617.2, U608.2 (IN_RAW); also elsewhere on the board
CLEARn: U609.1 (1CLR_N), U609.13 (2CLR_N), U612.8 (2Y_CLEAR_N)
CLOCK_PRESS: U609.11 (2CLK_PRESS), U614.4 (2Y_LOOP_B)
CLOCK_RELEASE: U609.3 (1CLK_RELEASE), U614.6 (1Y_LOOP_A)
CUT_A_CT: C623.1, U610.7 (CT)
CUT_A_QOD: R610.2, U610.5 (QOD)
CUT_B_CT: C624.1, U611.7 (CT)
CUT_B_QOD: R611.2, U611.5 (QOD)
GND: C602.2, C606.2, C607.2, C608.2, C609.2, C610.2, C611.2, C612.2, C613.2, C614.2, C615.2, C616.2, C620.2, C621.2, C622.2, C623.2, C624.2, J601.MP (MOUNT_GND), J602.MP (MOUNT_GND), J621.2, J621.MP (MOUNT_GND), J622.2, J622.MP (MOUNT_GND), R602.2, R604.2, R605.2, R612.2, R613.2, R614.2, R615.2, R618.2, R619.2, U602.2 (GND), U606.4 (GND), U606.9 (EP_GND), U607.2 (GND), U608.1 (GND), U609.7 (GND), U610.4 (GND), U611.4 (GND), U612.7 (GND), U613.2 (GND), U614.2 (GND), U615.7 (GND), U616.2 (GND); also elsewhere on the board
HOST_5V: C602.1, C610.1, C611.1, U602.1 (VIN), U610.1 (VBIAS), U611.1 (VBIAS); also elsewhere on the board
LID_FB: J622.4, TP603.1; also elsewhere on the board
LID_THERM_SEND: J602.2, J622.7, S602.NO (NO_LID_CLOSED)
LID_VOUT_DIV: J622.5, TP605.1; also elsewhere on the board
LOOP_5V: J601.1, J602.1, S601.C (COM), S602.C (COM), U602.5 (QOD), U602.6 (VOUT)
LOOP_A: U612.1 (1A), U613.6 (1Y_LOOP_A), U615.4 (2A); also elsewhere on the board
LOOP_A_RAW: J621.8, R614.1, U613.1 (1A_LOOP_A)
LOOP_B: U612.2 (1B), U613.4 (2Y_LOOP_B), U615.10 (3B); also elsewhere on the board
LOOP_B_RAW: J622.8, R615.1, U613.3 (2A_LOOP_B)
MCU_ARM: R604.1, U615.2 (1B); also elsewhere on the board
MCU_NRSTn: R606.2, TP601.1; also elsewhere on the board
MCU_STOPn: R605.1, U612.10 (2B); also elsewhere on the board
NTC_BASE: J621.6, TP606.1; also elsewhere on the board
NTC_LID: J622.6, TP607.1; also elsewhere on the board
RAW_SAFE: U612.6 (1Y_RAW_SAFE), U612.9 (2A), U616.3 (MR_N)
RELEASE_SEEN: U609.5 (1Q_RELEASE_SEEN), U615.1 (1A); also elsewhere on the board
SAFE_RESETn: R601.2, R606.1, U606.7 (WDO_N), U606.8 (ENOUT), U607.1 (RESET_N), U612.5 (1D); also elsewhere on the board
SOURCE_OK: R618.1, U602.3 (ON), U612.4 (1C), U615.5 (2B); also elsewhere on the board
UV_5V_LIMITED: C620.1, U610.2 (VIN); also elsewhere on the board
UV_5V_MID: C621.1, R610.1, U610.6 (VOUT), U611.2 (VIN)
UV_5V_SW: C622.1, J621.1, J622.1, R611.1, U611.6 (VOUT); also elsewhere on the board
UV_CTRL: J621.3, J622.3, U615.11 (4Y_UV_CTRL)
UV_DELAY_CT: R608.2, U616.4 (CT)
UV_DELAYn: R607.2, U612.12 (2C), U616.1 (RESET_N)
UV_GATE_A: R612.1, U610.8 (ON), U615.6 (2Y_CUT_A)
UV_GATE_B: R613.1, U611.8 (ON), U615.8 (3Y_CUT_B)
UV_POWER_GOOD: R616.2, U611.3 (PG), U615.13 (4B)
UV_RUN: U609.9 (2Q_UV_RUN), U615.9 (3A), U615.12 (4A); also elsewhere on the board
WDI: R602.1, U606.6 (WDI); also elsewhere on the board
WDT_CWD: R603.2, U606.2 (CWD)

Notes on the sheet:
HARDWARE INTERFACES: inputs3V3/HOST5/UV5LIMITED/SOURCE_OK fromdocksource. MCUinputsARM,STOPn,WDI defaultLOW. CENTERdebouncedOUT goes tosourceU114pin3; sourceU114pin4returnsBTN_CENTER_PRESSED. MCU_NRSTn isseparatefromSAFE_RESETn byR6061k tolimit100nF localresetcapdischarge.
DUALPHYSICALLOOPS: qualifiedHOST5 -> D2F NO -> respectiveUVmodule67L045NC -> LOOP_RAW ->430RGND. Thermostatlowlevelreference10mA: eachloop10.35mAmin/12.34mAmax. U602turnsloopsoff onlegacyUSB. DisconnectedwirepreventsUV. Bothlatchesclear onfault/STOP; watchdogrecoverygetsUVdelay. Release,thenfreshpr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
UV powercutsuseTPS22992lowRON insteadTPS22919. QOD330R ispopulated. PGonlygatesboostCTRL, notUV_RUN. Fullsource/cablelossbudget, hardwaretiming/shutdown opticaltail andsinglefaulttests remainunqualified. PWR_FLAGs identifyexternalrails inthisstandalonecandidate; theyarenotboardcomponents. NO steril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
